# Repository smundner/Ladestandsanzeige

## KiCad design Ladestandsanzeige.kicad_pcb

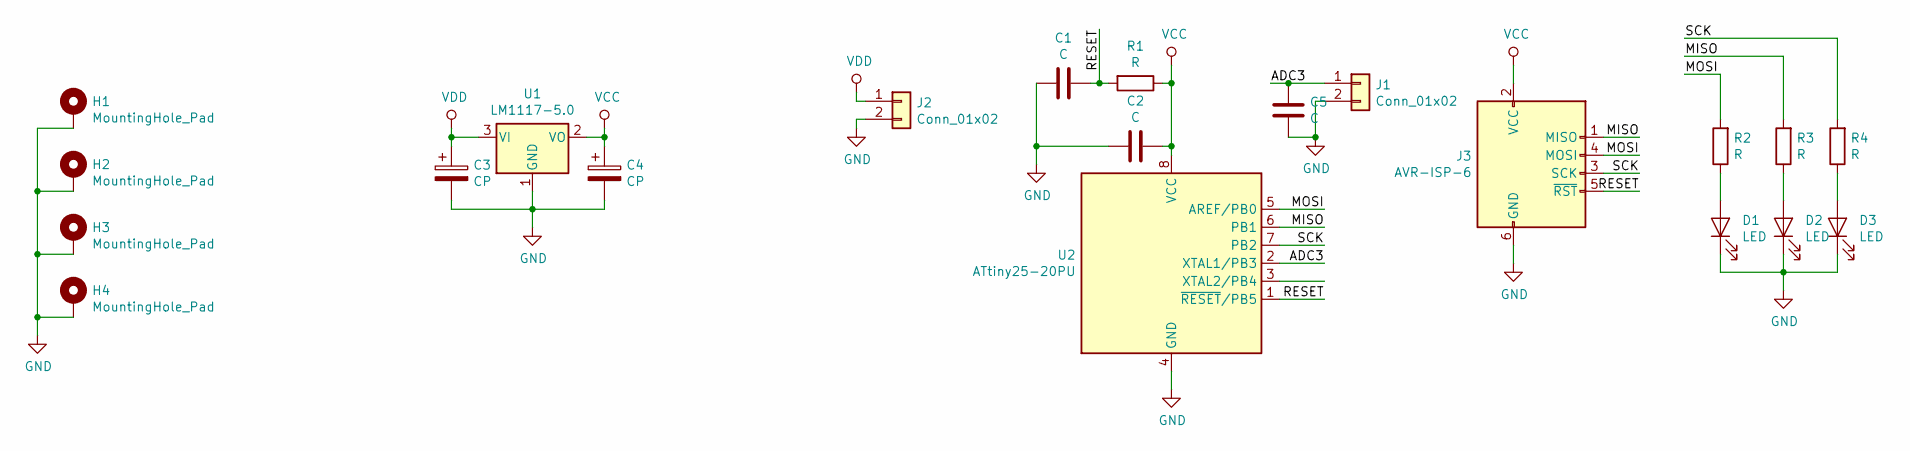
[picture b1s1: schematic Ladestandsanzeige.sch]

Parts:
C1, C2, C5: C; C_Disc_D3.0mm_W1.6mm_P2.50mm
C3, C4: CP; CP_EIA-3528-12_Kemet-T_Pad1.50x2.35mm_HandSolder
D1, D2, D3: LED; LED_D3.0mm
H1, H2, H3, H4: MountingHole_Pad; MountingHole_2.2mm_M2_Pad
J1, J2: Conn_01x02; JST_XH_B02B-XH-A_02x2.50mm_Straight
J3: AVR-ISP-6; PinHeader_2x03_P2.54mm_Vertical
R1, R2, R3, R4: R; R_Axial_DIN0204_L3.6mm_D1.6mm_P5.08mm_Horizontal
U1: LM1117-5.0; SOT-223-3Lead_TabPin2
U2: ATtiny25-20PU; DIP-8_W7.62mm

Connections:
/ADC3: C5.1, J1.1, U2.2 (XTAL1/PB3)
/MISO: J3.1 (MISO), R3.2, U2.6 (PB1)
/MOSI: J3.4 (MOSI), R2.2, U2.5 (AREF/PB0)
/RESET: C1.1, J3.5 (~RST), R1.2, U2.1 (~RESET~/PB5)
/SCK: J3.3 (SCK), R4.2, U2.7 (PB2)
GND: C1.2, C2.2, C3.2, C4.2, C5.2, D1.1 (K), D2.1 (K), D3.1 (K), H1.1, H2.1, H3.1, H4.1, J1.2, J2.2, J3.6 (GND), U1.1 (GND), U2.4 (GND)
unnamed: D1.2 (A), R2.1
unnamed: D2.2 (A), R3.1
unnamed: D3.2 (A), R4.1
VCC: C2.1, C4.1, J3.2 (VCC), R1.1, U1.2 (VO), U2.8 (VCC)
VDD: C3.1, J2.1, U1.3 (VI)

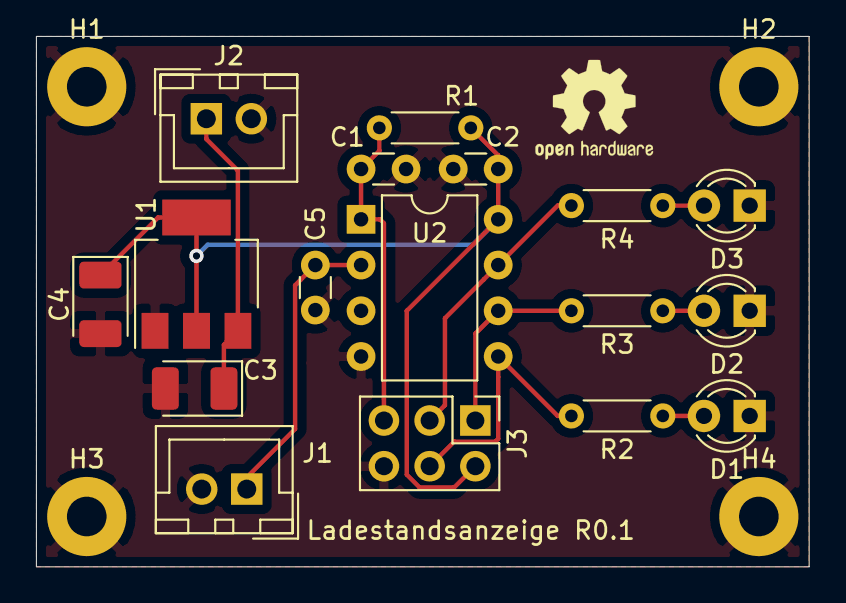
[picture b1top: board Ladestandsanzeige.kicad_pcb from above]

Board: 2 copper layers, 42.9 x 29.5 mm, 21 parts (0 on the bottom side), 11 nets.
